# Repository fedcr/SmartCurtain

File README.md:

## SmartCurtain

SmartCurtain is an open-source, automated curtain controller designed for smooth, quiet, and reliable operation. Built around the ESP32 microcontroller, it integrates stepper motor drive with stall detection, physical controls, Home Assistant integration via ESPHome/MQTT, and a modular 3D-printed transmission system.

---

## Features

- **Microcontroller:** ESP32-based core with Wi-Fi and Bluetooth connectivity.
- **Motor Control:** TMC2209 silent stepper motor driver for ultra-quiet movement, customizable microstepping, and stall detection.
- **Local Control:** Rotary encoder (EC11) with integrated push-button for local open/close and fine-tuning.
- **Smart Integration:** Fully compatible with Home Assistant (ESPHome / MQTT) for scheduled routines, presence detection, and sunrise/sunset automation.
- **Hardware & Enclosure:** Fully parametric 3D-printable parts designed in OpenSCAD with integrated cable routing, belt tensioning, and secure wall/track mounting.

---

## Repository Structure

├── BOM.csv                       # Project Bill of Materials
├── JOURNAL.md                   # Build log and design development notes
├── PCB/                         # KiCad design files, ERC/DRC reports
│   ├── SmartCurtain.kicad_sch   # Schematic file
│   ├── SmartCurtain.kicad_pcb   # PCB layout file
│   └── Fabrication/             # Gerbers, drill files, Pick & Place, BOM
├── Print Files/                 # 3D modeling source files and printable STLs
│   ├── smartcurtain.scad        # Parametric OpenSCAD master file
│   └── STL/                     # Ready-to-slice STL meshes
└── SmartCurtain_firmware/       # Source code and Home Assistant integration
    ├── SmartCurtain_firmware.ino
    └── SmartCurtain_configuration.yaml

---

## Hardware and Schematic
### Schematic Overview
The board integrates power regulation, the ESP32 module, the TMC2209 driver stage, and connectors for peripherals (encoder, endstops/sensors, mmWave presence sensor).

### PCB Layout and 3D Render
- Layers: 2-layer FR4 design
- Clearance & Trace Widths: Verified via KiCad DRC/ERC reports (see PCB/DRC.rpt and PCB/ERC.rpt)

## 3D Printing and Mechanical Assembly
All 3D parts are modeled in OpenSCAD and exported to Print Files/STL/:
- smartcurtain_base.stl and smartcurtain_lid.stl: Main electronics and motor enclosure.
- smartcurtain_drive_pulley.stl and smartcurtain_idler_pulley.stl: Timing belt drive system.
- smartcurtain_idler_bracket.stl and smartcurtain_idler_carriage.stl: Belt tensioner assembly.
- smartcurtain_trolley.stl and smartcurtain_track_adapter.stl: Curtain track mounting and trolley interface.
- smartcurtain_fit_test_coupon.stl and smartcurtain_pulley_coupon.stl: Quick test prints for verifying tolerances before full printing.

### Recommended Print Settings
- Material: PETG (recommended for heat and mechanical resistance)
- Layer Height: 0.20 mm
- Infill: 15% (Gyroid) (for the mechanical 100%)
- Perimeters/Walls: 4 walls for mechanical rigidity

## Firmware
1. Open SmartCurtain_firmware/SmartCurtain_firmware.ino in Arduino IDE or PlatformIO.
2. Install required dependencies (ESP32 board package, AccelStepper / TMCStepper).
3. Configure your pin definitions matching SmartCurtain.kicad_sch.

## Home Assistant Integration:
Import SmartCurtain_firmware/SmartCurtain_configuration.yaml into your ESPHome or Home Assistant configuration.
Follow on-screen discovery to calibrate travel limits and assign entities.

## Bill of Materials (BOM)
A complete breakdown of components, ratings, and part numbers can be found in 'BOM.csv' and 'PCB/Fabrication/SmartCurtain_BOM.csv'

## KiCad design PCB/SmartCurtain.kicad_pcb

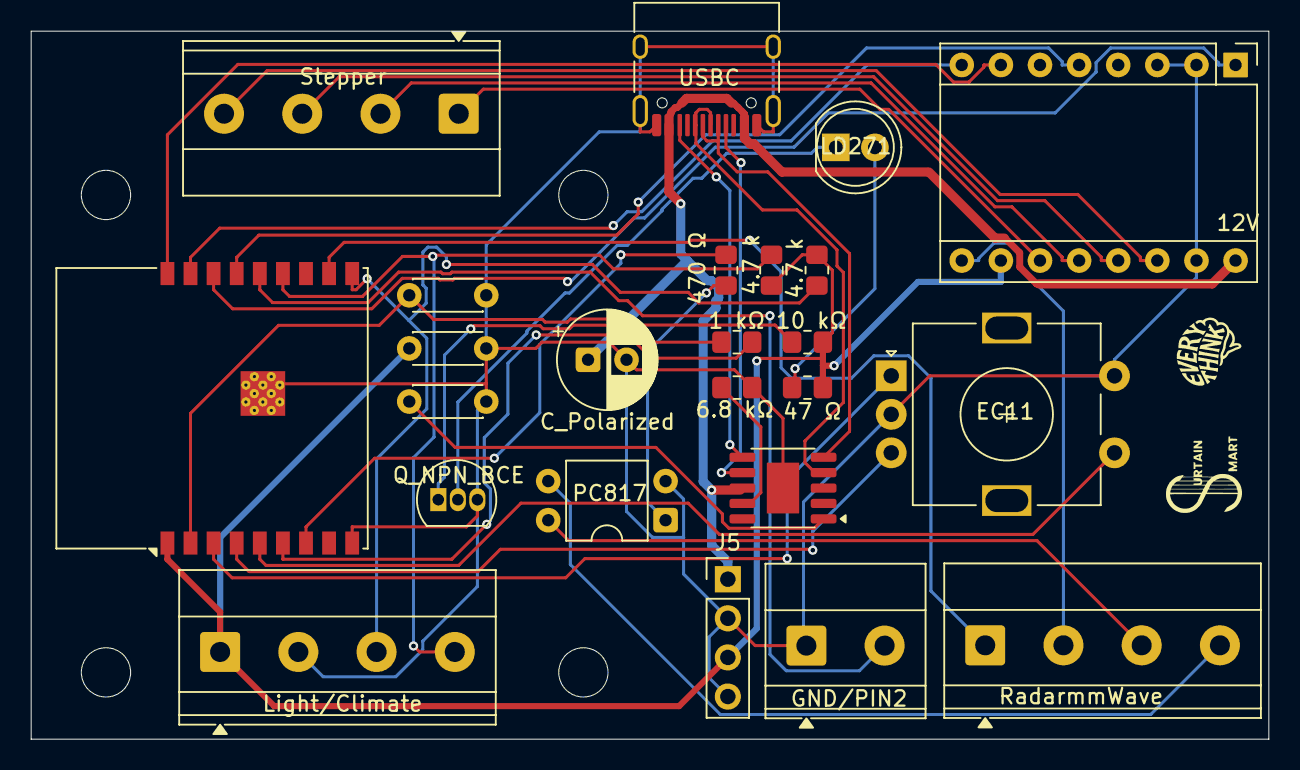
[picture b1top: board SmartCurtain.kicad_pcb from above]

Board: 2 copper layers, 80.4 x 46.0 mm, 28 parts (0 on the bottom side), 33 nets.

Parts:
1 kΩ: 1 kΩ; R_0805_2012Metric_Pad1.20x1.40mm_HandSolder
4.7 k, 4.7 k#2: 4.7 k; R_0805_2012Metric_Pad1.20x1.40mm_HandSolder
6.8 kΩ: 6.8 kΩ; R_0805_2012Metric_Pad1.20x1.40mm_HandSolder
10 kΩ: 10 kΩ; R_0805_2012Metric_Pad1.20x1.40mm_HandSolder
47 Ω: 22 Ω - 47 Ω; R_0805_2012Metric_Pad1.20x1.40mm_HandSolder
470 Ω: 470 Ω; R_0805_2012Metric_Pad1.20x1.40mm_HandSolder
C4, C6: C; C_Disc_D4.3mm_W1.9mm_P5.00mm
C5: 100nF; C_Disc_D4.3mm_W1.9mm_P5.00mm
C_Polarized: C_Polarized; CP_Radial_D6.3mm_P2.50mm
EC11: RotaryEncoder_Switch; RotaryEncoder_Alps_EC11E-Switch_Vertical_H20mm
H1, H2, H3, H4: MountingHole; MountingHole_3.2mm_M3
J1: Stepper; TerminalBlock_Phoenix_MKDS-1,5-4-5.08_1x04_P5.08mm_Horizont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
J5: Mini360_Buck; PinHeader_1x04_P2.54mm_Vertical
LD271: LD271; LED_D5.0mm_IRGrey
Light/Climate: Screw_Terminal_01x04; TerminalBlock_Phoenix_MKDS-1,5-4-5.08_1x04_P5.08mm_Horizont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
Q1: Q_NPN_BCE; TO-92L_Inline
RadarmmWave: Screw_Terminal_01x02; TerminalBlock_Phoenix_MKDS-1,5-2-5.08_1x02_P5.08mm_Horizont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
RadarmmWave1: Screw_Terminal_01x04; TerminalBlock_Phoenix_MKDS-1,5-4-5.08_1x04_P5.08mm_Horizont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
U1: ESP32-C3-WROOM-02
U2: CH224K; SSOP-10-1EP_3.9x4.9mm_P1mm_EP2.1x3.3mm
U3: TMC2209_StepStick; Pololu_Breakout-16_15.2x20.3mm
U4: PC817; DIP-4_W7.62mm
USBC: USB_C_Receptacle_USB2.0_16P; USB_C_Receptacle_HRO_TYPE-C-31-M-12

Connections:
+3V3: 4.7 k.1, 4.7 k#2.2, 10 kΩ.1, 47 Ω.1, C5.1, J5.3, Light/Climate.1, U1.1 (3V3), U3.10 (VIO)
+12V: C_Polarized.1, J5.1, U2.8 (VBUS), U3.16 (VMOT), USBC.A4 (VBUS), USBC.A9 (VBUS), USBC.B4 (VBUS), USBC.B9 (VBUS)
GND: 6.8 kΩ.1, C4.2, C5.2, C6.2, C_Polarized.2, EC11.C, EC11.S2, J5.2, J5.4, Light/Climate.2, Q1.3 (E), RadarmmWave.1, RadarmmWave1.2, U1.9 (GND), U1.19 (GND), U2.11 (GND), U3.2 (MS1), U3.3 (MS2), U3.9 (GND), U3.15 (GND_MOT), U4.2, USBC.A1 (GND), USBC.A12 (GND), USBC.B1 (GND), USBC.B12 (GND), USBC.SH (SHIELD)
unnamed: 47 Ω.2, LD271.2 (A)
unnamed: LD271.1 (K), Q1.2 (C)
unnamed: J1.1, U3.11 (1B)
unnamed: J1.2, U3.12 (1A)
unnamed: J1.3, U3.13 (2A)
unnamed: J1.4, U3.14 (2B)
unnamed: U2.7 (CC1), USBC.A5 (CC1)
unnamed: U2.6 (CC2), USBC.B5 (CC2)
unnamed: RadarmmWave.2, U1.14 (IO19)
unnamed: 4.7 k#2.1, Light/Climate.3, U1.10 (IO10)
unnamed: 4.7 k.2, Light/Climate.4, U1.13 (IO18)
unnamed: 1 kΩ.2, Q1.1 (B)
unnamed: 470 Ω.1, U4.1
unnamed: RadarmmWave1.1, U1.11 (IO20/RXD)
unnamed: RadarmmWave1.3, U4.4
unnamed: RadarmmWave1.4, U4.3
unnamed: 10 kΩ.2, C4.1, U1.2 (EN)
unnamed: U1.18 (IO0), U3.7 (STEP)
unnamed: U1.17 (IO1), U3.8 (DIR)
unnamed: U1.16 (IO2), U3.1 (EN)
unnamed: U1.15 (IO3), U3.5 (DIAG)
unnamed: EC11.A, U1.3 (IO4)
unnamed: EC11.B, U1.4 (IO5)
unnamed: EC11.S1, U1.5 (IO6)
unnamed: 1 kΩ.1, U1.6 (IO7)
unnamed: 470 Ω.2, U1.7 (IO8)
unnamed: 6.8 kΩ.2, U2.9 (CFG1)
unnamed: U2.5 (DM), USBC.A7 (D-), USBC.B7 (D-)
unnamed: U2.4 (DP), USBC.A6 (D+), USBC.B6 (D+)
unnamed: C6.1, U2.1 (VDD)
